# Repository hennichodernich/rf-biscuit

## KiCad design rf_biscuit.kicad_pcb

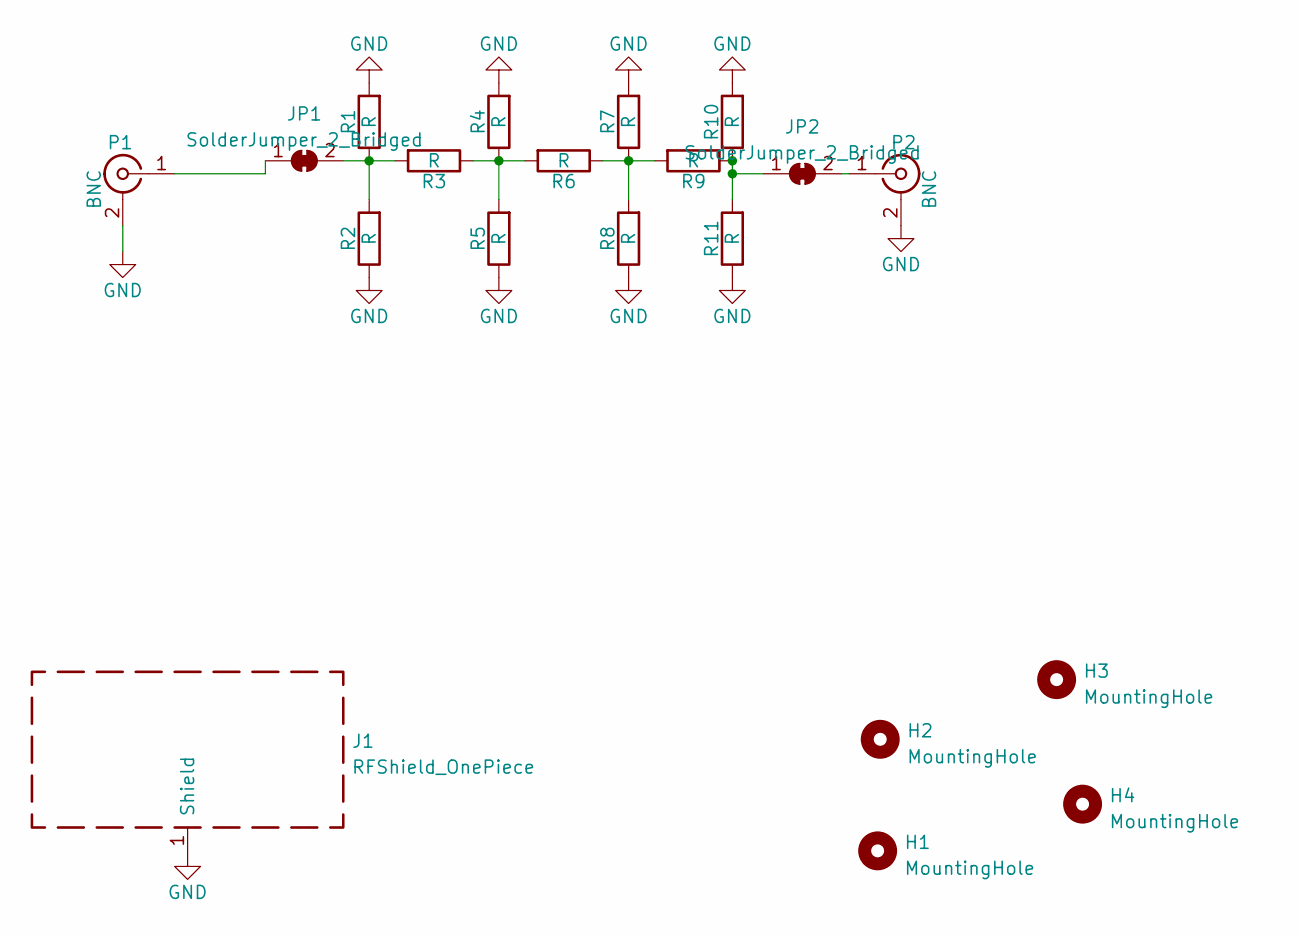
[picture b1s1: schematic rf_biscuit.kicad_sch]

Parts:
H1, H2, H3, H4: MountingHole; MountingHole_3.2mm_M3
J1: RFShield_OnePiece; Wuerth_36103205_20x20mm
JP1, JP2: SolderJumper_2_Bridged; SolderJumper-2_P1.3mm_Bridged2Bar_Pad1.0x1.5mm
P1, P2: BNC; SMA_Samtec_SMA-J-P-X-ST-EM1_EdgeMount
R1, R2, R4, R5, R7, R8, R10, R11: R; L_0805_2012Metric_Pad1.15x1.40mm_HandSolder
R3, R6, R9: R; L_1008_0805_0603_HandSolder_Combo

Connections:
GND: J1.1 (Shield), P1.2 (Ext), P2.2 (Ext), R1.2, R2.1, R4.2, R5.1, R7.2, R8.1, R10.2, R11.1
unnamed: JP1.1 (A), P1.1 (In)
unnamed: JP1.2 (B), R1.1, R2.2, R3.2
unnamed: JP2.1 (A), R9.1, R10.1, R11.2
unnamed: JP2.2 (B), P2.1 (In)
unnamed: R3.1, R4.1, R5.2, R6.2
unnamed: R6.1, R7.1, R8.2, R9.2

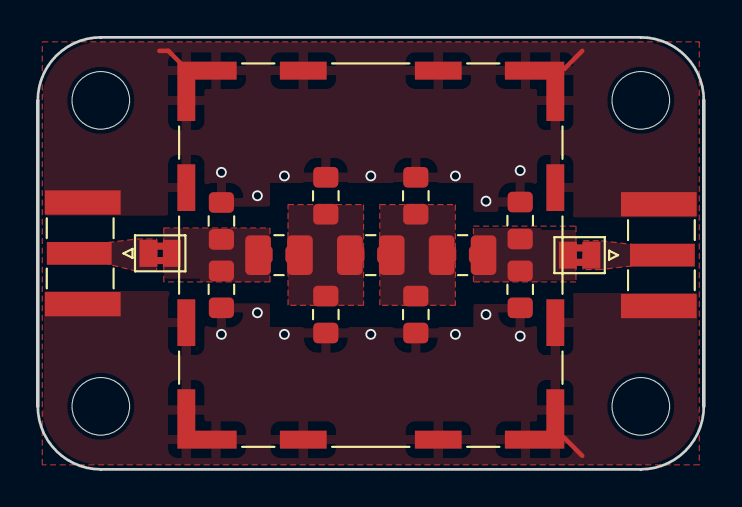
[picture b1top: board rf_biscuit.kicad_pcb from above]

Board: 2 copper layers, 37.0 x 24.0 mm, 20 parts (0 on the bottom side), 7 nets.

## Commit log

2022-08-30 Heavily modified and updated to KiCAD 6.0

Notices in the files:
rf_biscuit.kicad_pcb:
CC BY-SA 3.0
